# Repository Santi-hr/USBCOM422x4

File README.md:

# USBCOM422x4
Simple 4 channel USB to RS422 serial converter module board, based on the XR21B1424 USB UART Bridge.
When connected to a PC four virtual COM ports are available for communication with serial devices.

The board is inspired on a similar RS422 converter, but more robust and with updated functionalities:
* A more modern USB-C connector
* A newer, compact and more robust USB-Serial bridge IC
  * Includes ±15kV ESD on USB lines
  * Internally provides all necessary functionality (48MHz clock, regulator, drivers) which simplifies the design and minimizes component failures.
* A sightly more protected power input using a TVS, a PPTC and an improved LDO.
* Supports USB suspend mode, disabling the transceivers when no USB bus activity is detected.
* Pinout printed on bottom silkscreen. 

## Drivers
The USB Bridge chip can use the native OS CDC-ACM.
However, using the MaxLinear supplied custom drivers is recommended.

Get the latest drivers from their web, under "Documentation & Design Tools":
https://www.maxlinear.com/product/interface/uarts/usb-uarts/xr21b1424

A copy of the drivers used to test the board can be found in the [drivers](drivers) folder.

## Technical details

### Pinout
### USB
Standard 16 pin USB-C connector for use as a USB 2.0 full speed device (MBs).

### RS422 Serial port

Each serial port interface uses a DE-9 male connector.

| Pin | Signal | Direction | Description             |
|-----|-------|-----------|-------------------------|
| 1   | TX-   | O         | Data output, negative   |
| 2   | TX+   | O         | Data output, positive   |
| 3   | RX+   | I         | Data input, positive    |
| 4   | RX-   | I         | Data input, negative    |
| 5   | GND   | -         | Signal ground           |
| 6   | RTS-  | O         | Ready to send, negative |
| 7   | RTS+  | O         | Ready to send, positive |
| 8   | CTS+  | I         | Clear to send, positive |
| 9   | CTS-  | I         | Clear to send, negative |

### HMI

| LED       | Color  | Meaning                                                                                             |
|-----------|--------|-----------------------------------------------------------------------------------------------------|
| POWER LDO | Yellow | On when power is being provided to RS422 transceivers. Should be on when not in suspend mode.       |
| POWER U1  | Yellow | On when USB-UART Bridge chip is powered. Should be always with the USB cable plugged                |
| TX        | Red    | Led toggles at a rate of approximately 10 Hz whenever the corresponding UART transmit pin is active |
| RX        | Green  | Led toggles at a rate of approximately 10 Hz whenever the corresponding UART receive pin is active  |

### Mechanical

Dimensions in mm.

## Design notes

This board currently has not been tested for EMI/EMC compliance. Could generate or be affected by radio interferences.

The design only uses two layers in order to reduce manufacturing costs.
To get a cleaner layout and reduce possible EMI effects the stackup can be increased to 4 layers. 
Also size could be optimized and reduced, the current form factor follows the board I was trying to replace.

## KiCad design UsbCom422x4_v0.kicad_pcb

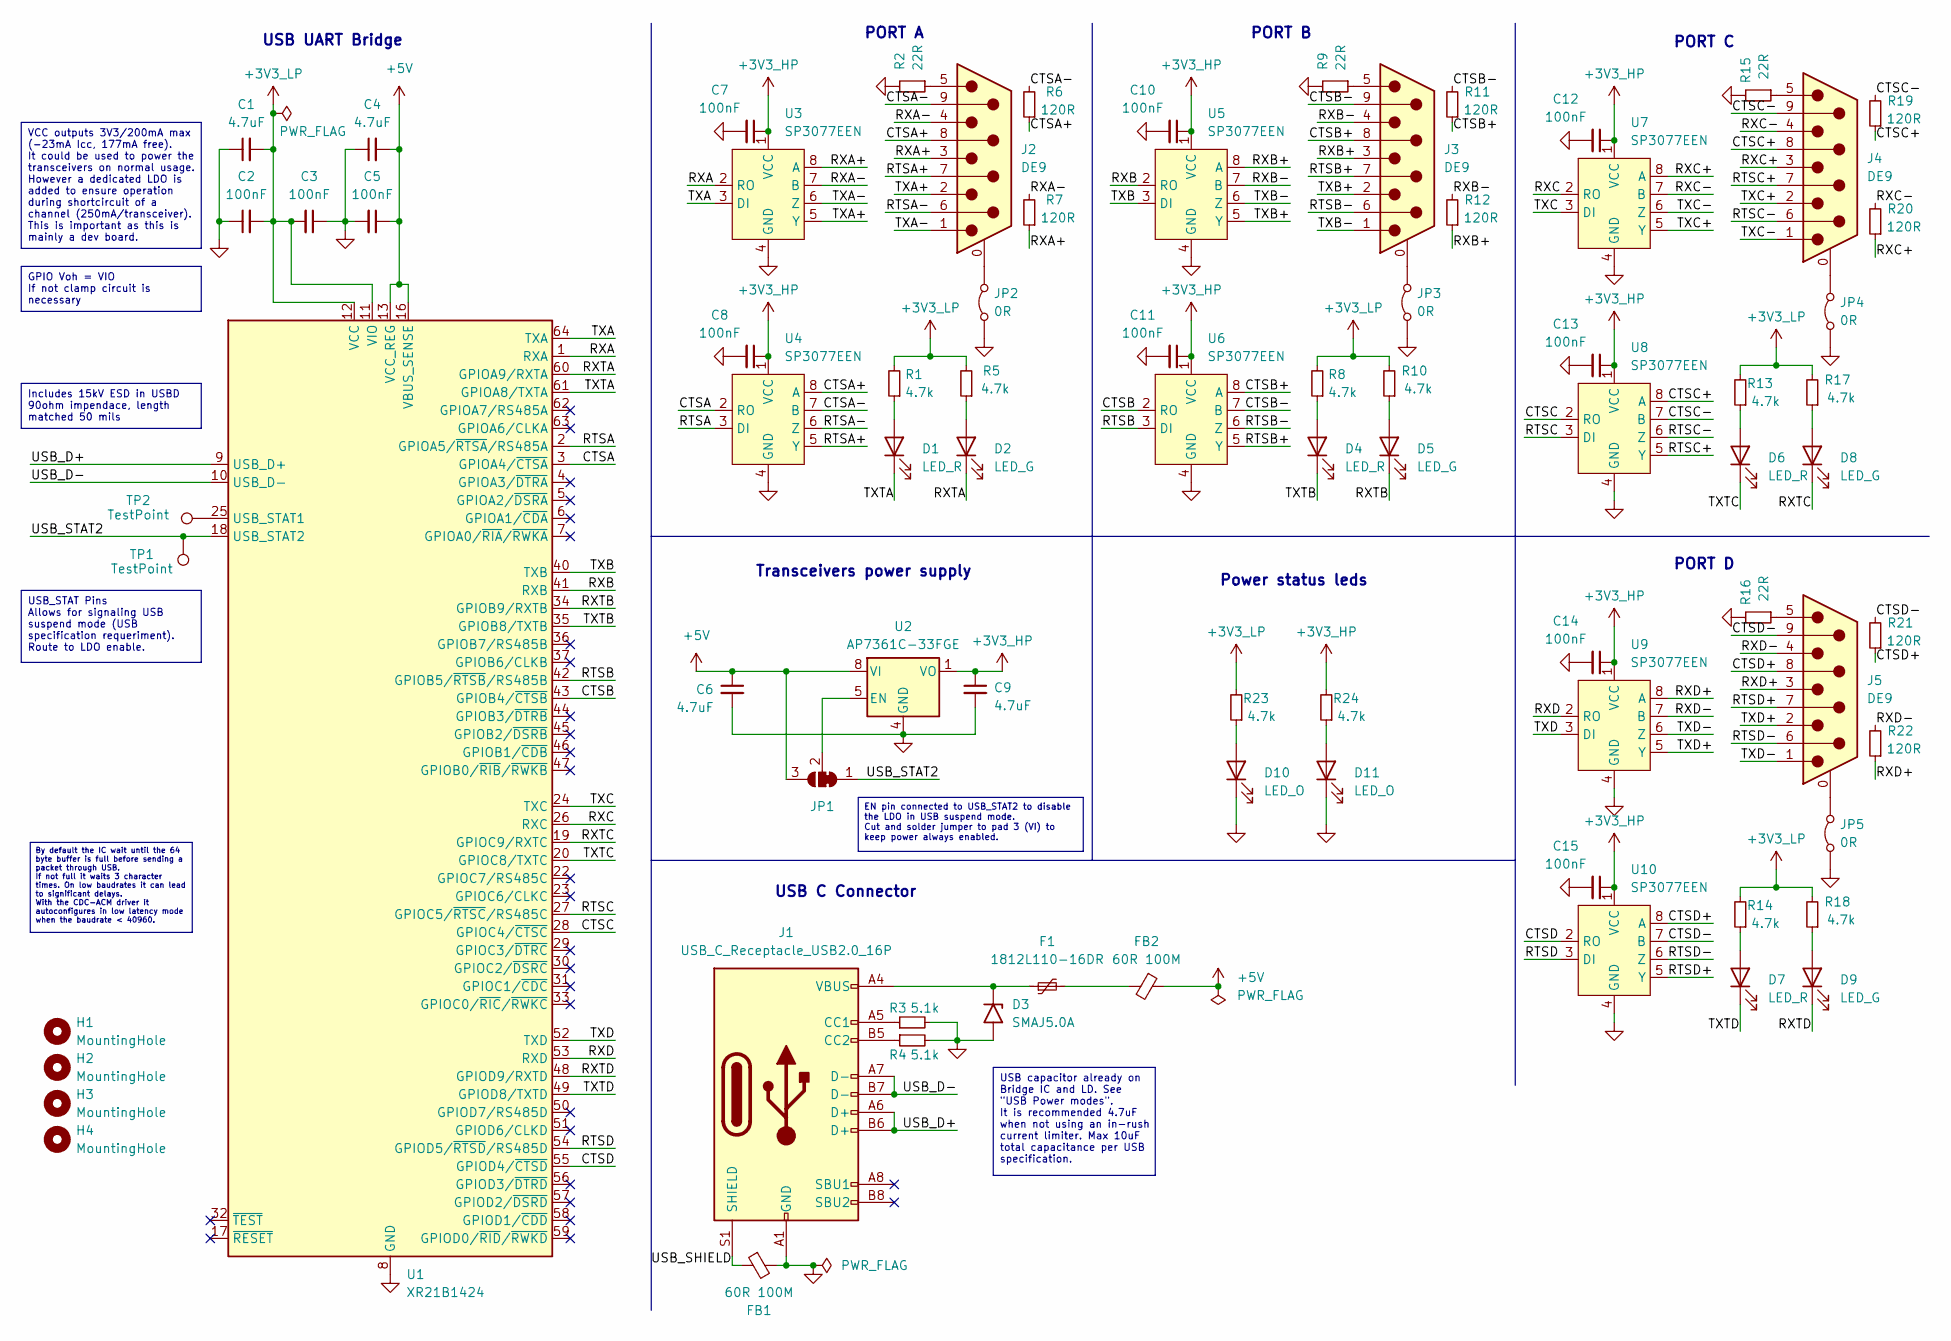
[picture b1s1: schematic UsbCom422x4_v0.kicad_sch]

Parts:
C1, C4, C6, C9: 4.7uF; C_0805_2012Metric
C2, C3, C5, C7, C8, C10, C11, C12, C13, C14, C15: 100nF; C_0603_1608Metric
D1, D4, D6, D7: LED_R; LED_0805_2012Metric
D2, D5, D8, D9: LED_G; LED_0805_2012Metric
D3: SMAJ5.0A; D_SMA
D10, D11: LED_O; LED_0805_2012Metric
F1: 1812L110-16DR; R_1812_4532Metric
FB1, FB2: 60R 100M; R_0805_2012Metric
H1, H2, H3, H4: MountingHole; MountingHole_4.3mm_M4
J1: USB_C_Receptacle_USB2.0_16P; USB_C_Receptacle_GCT_USB4105-xx-A_16P_TopMnt_Horizontal
J2, J3, J4, J5: DE9; DSUB-9_Male_Vertical_P2.77x2.84mm_MountingHoles
JP1: SolderJumper_3_Bridged12; SolderJumper-3_P1.3mm_Bridged12_RoundedPad1.0x1.5mm
JP2, JP3, JP4, JP5: 0R; R_0805_2012Metric
R1, R5, R8, R10, R13, R14, R17, R18, R23, R24: 4.7k; R_0603_1608Metric
R2, R9, R15, R16: 22R; R_0805_2012Metric
R3, R4: 5.1k; R_0603_1608Metric
R6, R7, R11, R12, R19, R20, R21, R22: 120R; R_1206_3216Metric
TP1, TP2: TestPoint; TestPoint_Pad_D1.0mm
U1: XR21B1424; LQFP-64_10x10mm_P0.5mm
U2: AP7361C-33FGE; U-DFN3030-8_AP7361C
U3, U4, U5, U6, U7, U8, U9, U10: SP3077EEN; SOIC-8_3.9x4.9mm_P1.27mm

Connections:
+3V3_HP: C7.1, C8.1, C9.1, C10.1, C11.1, C12.1, C13.1, C14.1, C15.1, R24.2, U2.1 (VO), U3.1 (VCC), U4.1 (VCC), U5.1 (VCC), U6.1 (VCC), U7.1 (VCC), U8.1 (VCC), U9.1 (VCC), U10.1 (VCC)
+3V3_LP: C1.2, C2.2, C3.2, R1.2, R5.2, R8.2, R10.2, R13.2, R14.2, R17.2, R18.2, R23.2, U1.11 (VIO), U1.12 (VCC), U1.38 (VIO)
+5V: C4.2, C5.1, C6.1, FB2.1, JP1.3 (B), U1.13 (VCC_REG), U1.16 (VBUS_SENSE), U2.8 (VI)
/CTSA: U1.3 (GPIOA4/~CTSA), U4.2 (RO)
/CTSA+: J2.8, R6.1, U4.8 (A)
/CTSA-: J2.9, R6.2, U4.7 (B)
/CTSB: U1.43 (GPIOB4/~CTSB), U6.2 (RO)
/CTSB+: J3.8, R11.1, U6.8 (A)
/CTSB-: J3.9, R11.2, U6.7 (B)
/CTSC: U1.28 (GPIOC4/~CTSC), U8.2 (RO)
/CTSC+: J4.8, R19.1, U8.8 (A)
/CTSC-: J4.9, R19.2, U8.7 (B)
/CTSD: U1.55 (GPIOD4/~CTSD), U10.2 (RO)
/CTSD+: J5.8, R21.1, U10.8 (A)
/CTSD-: J5.9, R21.2, U10.7 (B)
/RTSA: U1.2 (GPIOA5/~RTSA/RS485A), U4.3 (DI)
/RTSA+: J2.7, U4.5 (Y)
/RTSA-: J2.6, U4.6 (Z)
/RTSB: U1.42 (GPIOB5/~RTSB/RS485B), U6.3 (DI)
/RTSB+: J3.7, U6.5 (Y)
/RTSB-: J3.6, U6.6 (Z)
/RTSC: U1.27 (GPIOC5/~RTSC/RS485C), U8.3 (DI)
/RTSC+: J4.7, U8.5 (Y)
/RTSC-: J4.6, U8.6 (Z)
/RTSD: U1.54 (GPIOD5/~RTSD/RS485D), U10.3 (DI)
/RTSD+: J5.7, U10.5 (Y)
/RTSD-: J5.6, U10.6 (Z)
/RXA: U1.1 (RXA), U3.2 (RO)
/RXA+: J2.3, R7.1, U3.8 (A)
/RXA-: J2.4, R7.2, U3.7 (B)
/RXB: U1.41 (RXB), U5.2 (RO)
/RXB+: J3.3, R12.1, U5.8 (A)
/RXB-: J3.4, R12.2, U5.7 (B)
/RXC: U1.26 (RXC), U7.2 (RO)
/RXC+: J4.3, R20.1, U7.8 (A)
/RXC-: J4.4, R20.2, U7.7 (B)
/RXD: U1.53 (RXD), U9.2 (RO)
/RXD+: J5.3, R22.1, U9.8 (A)
/RXD-: J5.4, R22.2, U9.7 (B)
/RXTA: D2.1 (K), U1.60 (GPIOA9/RXTA)
/RXTB: D5.1 (K), U1.34 (GPIOB9/RXTB)
/RXTC: D8.1 (K), U1.19 (GPIOC9/RXTC)
/RXTD: D9.1 (K), U1.48 (GPIOD9/RXTD)
/TXA: U1.64 (TXA), U3.3 (DI)
/TXA+: J2.2, U3.5 (Y)
/TXA-: J2.1, U3.6 (Z)
/TXB: U1.40 (TXB), U5.3 (DI)
/TXB+: J3.2, U5.5 (Y)
/TXB-: J3.1, U5.6 (Z)
/TXC: U1.24 (TXC), U7.3 (DI)
/TXC+: J4.2, U7.5 (Y)
/TXC-: J4.1, U7.6 (Z)
/TXD: U1.52 (TXD), U9.3 (DI)
/TXD+: J5.2, U9.5 (Y)
/TXD-: J5.1, U9.6 (Z)
/TXTA: D1.1 (K), U1.61 (GPIOA8/TXTA)
/TXTB: D4.1 (K), U1.35 (GPIOB8/TXTB)
/TXTC: D6.1 (K), U1.20 (GPIOC8/TXTC)
/TXTD: D7.1 (K), U1.49 (GPIOD8/TXTD)
/USB_D+: J1.A6 (D+), J1.B6 (D+), U1.9 (USB_D+)
/USB_D-: J1.A7 (D-), J1.B7 (D-), U1.10 (USB_D-)
/USB_SHIELD: FB1.1, J1.S1 (SHIELD)
/USB_STAT2: JP1.1 (A), TP1.1, U1.18 (USB_STAT2)
GND: C1.1, C2.1, C3.1, C4.1, C5.2, C6.2, C7.2, C8.2, C9.2, C10.2, C11.2, C12.2, C13.2, C14.2, C15.2, D3.2 (A2), D10.1 (K), D11.1 (K), FB1.2, J1.A1 (GND), J1.A12 (GND), J1.B1 (GND), J1.B12 (GND), JP2.1 (A), JP3.1 (A), JP4.1 (A), JP5.1 (A), R2.2, R3.2, R4.2, R9.2, R15.2, R16.2, U1.8 (GND), U1.14 (GND), U1.15 (GND), U1.21 (GND), U1.39 (GND), U2.4 (GND), U2.9 (GND), U3.4 (GND), U4.4 (GND), U5.4 (GND), U6.4 (GND), U7.4 (GND), U8.4 (GND), U9.4 (GND), U10.4 (GND)
unnamed: D1.2 (A), R1.1
unnamed: D2.2 (A), R5.1
unnamed: D3.1 (A1), F1.1, J1.A4 (VBUS), J1.A9 (VBUS), J1.B4 (VBUS), J1.B9 (VBUS)
unnamed: D4.2 (A), R8.1
unnamed: D5.2 (A), R10.1
unnamed: D6.2 (A), R13.1
unnamed: D7.2 (A), R14.1
unnamed: D8.2 (A), R17.1
unnamed: D9.2 (A), R18.1
unnamed: D10.2 (A), R23.1
unnamed: D11.2 (A), R24.1
unnamed: F1.2, FB2.2
unnamed: J1.A5 (CC1), R3.1
unnamed: J1.B5 (CC2), R4.1
unnamed: J2.0 (PAD), JP2.2 (B)
unnamed: J2.5, R2.1
unnamed: J3.0 (PAD), JP3.2 (B)
unnamed: J3.5, R9.1
unnamed: J4.0 (PAD), JP4.2 (B)
unnamed: J4.5, R15.1
unnamed: J5.0 (PAD), JP5.2 (B)
unnamed: J5.5, R16.1
unnamed: JP1.2 (C), U2.5 (EN)
unnamed: TP2.1, U1.25 (USB_STAT1)

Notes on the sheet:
EN pin connected to USB_STAT2 to disable the LDO in USB suspend mode. Cut and solder jumper to pad 3 (VI) to keep power always enabled.
USB_STAT Pins Allows for signaling USB suspend mode (USB specification requeriment). Route to LDO enable.
USB capacitor already on Bridge IC and LD. See "USB Power modes". It is recommended 4.7uF when not using an in-rush current limiter. Max 10uF total capacitance per USB specification.
By default the IC wait until the 64 byte buffer is full before sending a packet through USB. If not full it waits 3 character times. On low baudrates it can lead to significant delays. With the CDC-ACM driver it autoconfigures in low latency mode when the baudrate < 40960.
VCC outputs 3V3/200mA max (-23mA Icc, 177mA free). It could be used to power the transceivers on normal usage. However a dedicated LDO is added to ensure operation during shortcircuit of a channel (250mA/transceiver). This is important as this is mainly a dev board.
Includes 15kV ESD in USBD 90ohm impendace, length matched 50 mils
GPIO Voh = VIO If not clamp circuit is necessary
PORT D
PORT B
PORT A
USB UART Bridge
Power status leds
Transceivers power supply
PORT C
USB C Connector

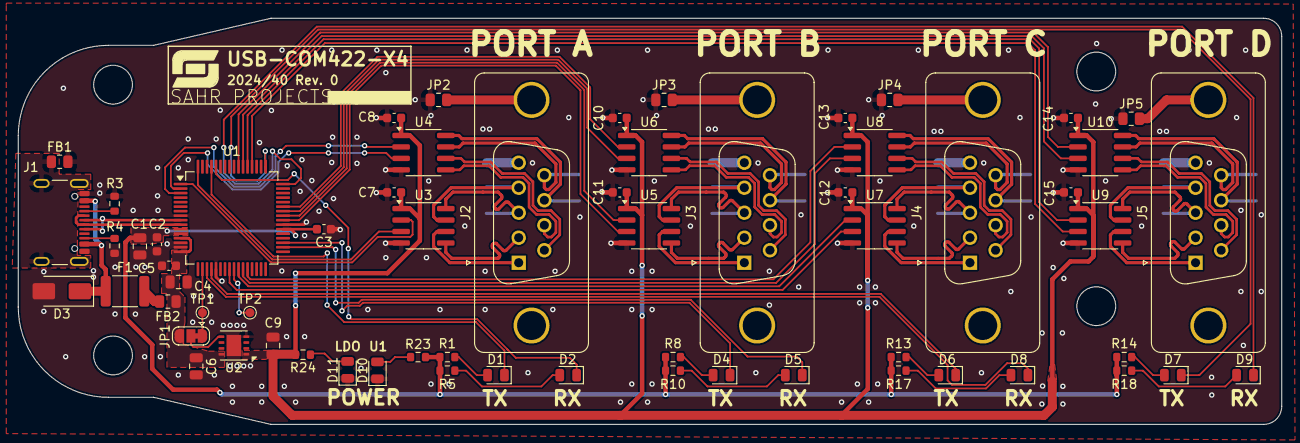
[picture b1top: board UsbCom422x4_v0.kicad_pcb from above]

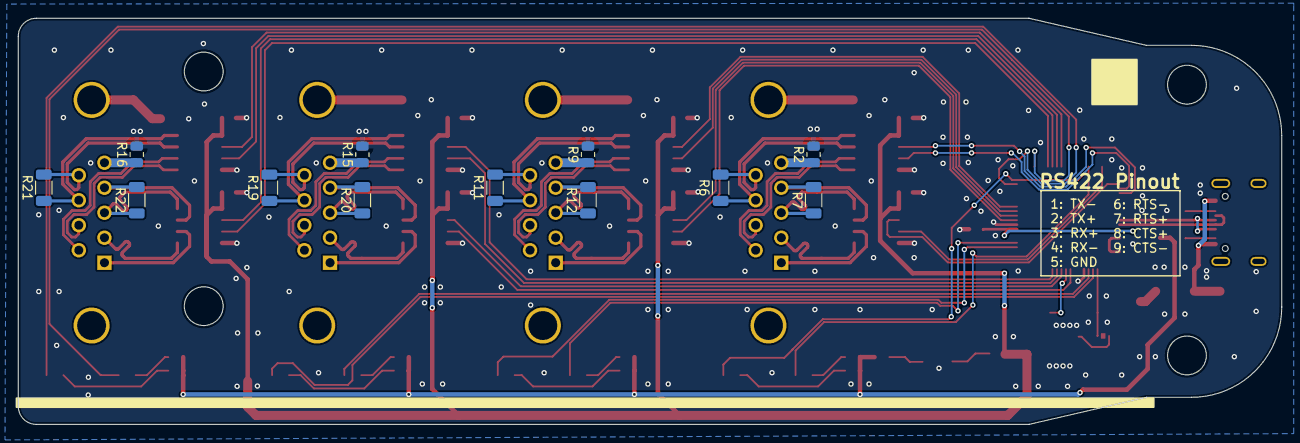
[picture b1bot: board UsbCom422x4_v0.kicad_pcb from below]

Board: 2 copper layers, 140.0 x 45.0 mm, 79 parts (12 on the bottom side), 88 nets.

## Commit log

2025-01-03 Create LICENSE
2025-01-04 Add first version
